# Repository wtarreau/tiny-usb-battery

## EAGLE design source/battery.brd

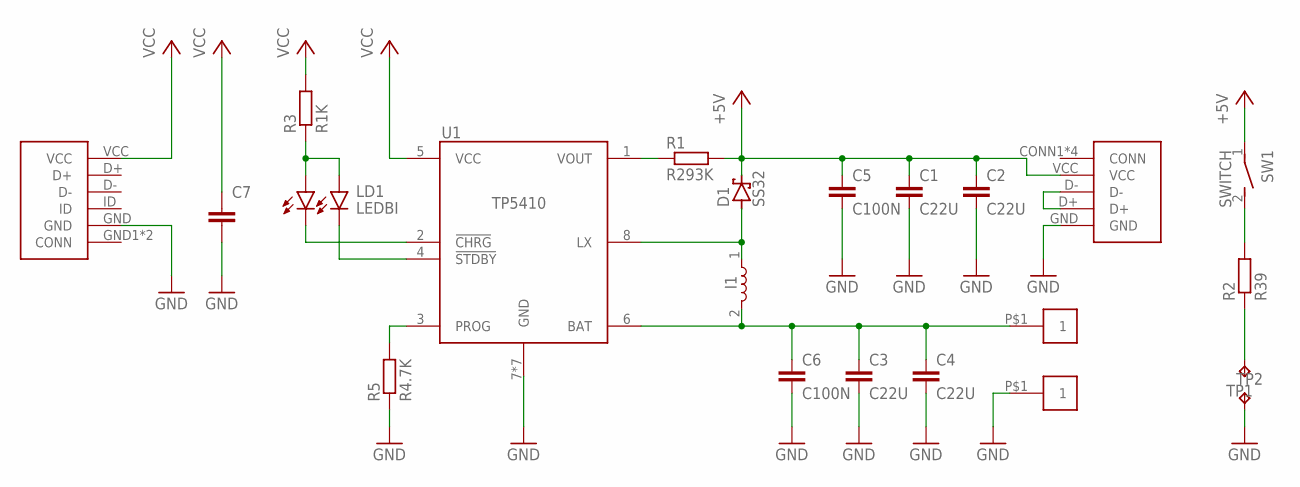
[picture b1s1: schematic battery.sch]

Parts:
BAT+: PIN
C1, C2, C3, C4: C22U; CAPC2214X120
C5, C6: C100N; CAPC1508X45
C7: C-EUC0603K; C0603K
D1: SS32; DIOM6859X265
I1: IND47M; DR73
LD1: LEDBI; LEDBI0603
R1: R293K; RESC1508X30
R2: R39; RESC3116X40
R3: R1K; RESC1508X30
R5: R4.7K; RESC1508X30
SW1: SWITCH; BUTTON
TP1, TP2: TPB1,27; B1,27
U1: TP5410; SOIC127P600X175-8
U$1: USB20
U$3: MICRO-USB
U$5: PIN

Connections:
+5V: C1.1, C2.1, C5.1, D1.1 (C), R1.2, SW1.1, U$1.VCC
CHRG: LD1.K1, U1.2 (!CHRG)
GND: C1.2, C2.2, C3.2, C4.2, C5.2, C6.2, C7.2, R5.1, TP2.TP, U1.7 (GND), U1.GND1 (GND), U1.GND2 (GND), U1.GND3 (GND), U1.GND4 (GND), U1.GND5 (GND), U1.GND6 (GND), U$1.GND, U$3.GND, U$5.P$1
LEDCOMM: LD1.A1, LD1.A2, R3.1
LX: D1.2 (A), I1.1, U1.8 (LX)
unnamed: U$1.D+, U$1.D-
unnamed: R2.2, SW1.2 (S)
unnamed: R2.1, TP1.TP
PROG: R5.2, U1.3 (PROG)
STDBY: LD1.K2, U1.4 (!STDBY)
VBAT: BAT+.P$1, C3.1, C4.1, C6.1, I1.2, U1.6 (BAT)
VCC: C7.1, R3.2, U1.5 (VCC), U$3.VCC
VOUT: R1.1, U1.1 (VOUT)

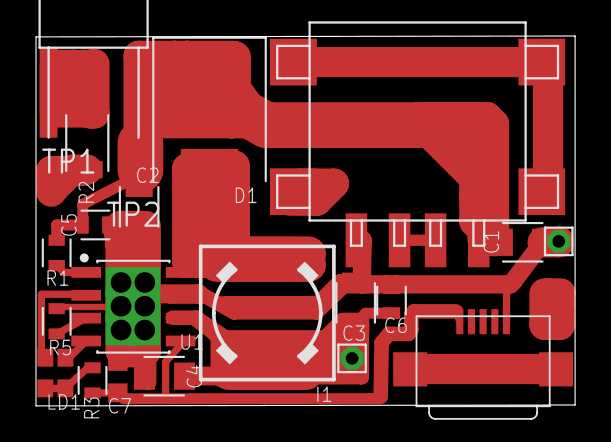
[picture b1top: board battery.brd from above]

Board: 2 copper layers, 29.9 x 20.6 mm, 22 parts (0 on the bottom side), 13 nets.

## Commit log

2020-04-26 Import last version of the source files
    These were made using Eagle v7 so they should work with about any current
    version.
2020-04-26 Import rendered files
    In the "output" directory we have the PCB in png (1200 DPI) and PDF
    formats, as well as the schmeatic, parts list and component placement.
    This should help anyone rebuild one without installing any software.
2024-01-07 Update source to v11 of the project
    Minor updates.
2024-01-07 Update to v12 of the project
    This slightly rearranges certain tracks to ease laser engraving,
    manual components placement and soldering.
